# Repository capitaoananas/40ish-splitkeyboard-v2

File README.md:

# 40%ish Split Keyboard V2

A minimalist, 36-key split keyboard with 18 keys per half.

This is the **second generation** of the 40%ish split keyboard — an open-source, wireless-capable, DIY mechanical keyboard built for compact typing and clean design.

---

## What's New in V2

- **Easier reversing** – solder bridges allow mirrored PCB assembly without flipping the MCU
- **Wireless support** – built for the Nice!Nano V2 with RMK firmware and VIA configurability
- **Sandwich case support** – mounting holes added for plate/PCB/plate builds

---

## Features

- **Split layout** – 18 keys per side (36 total), column-staggered
- **MX hotswap** – change your switches anytime, no soldering needed
- **Wireless** – powered by Nice!Nano V2 + ZMK or RMK
- **Fully open-source** – PCB, firmware, case files

---

## Bill of Materials (BOM)
| Part                                 | Quantity | Price  | Link                                                                                                                                                                                                                                                                                                                                                                                                                                                                                          | Notes                                                      |
| ------------------------------------ | -------- | ------ | --------------------------------------------------------------------------------------------------------------------------------------------------------------------------------------------------------------------------------------------------------------------------------------------------------------------------------------------------------------------------------------------------------------------------------------------------------------------------------------------- | ---------------------------------------------------------- |
| PCB                                  | 5        | $19.31 | [JLCPCB](https://jlcpcb.com/)                                                                                                                                                                                                                                                                                                                                                                                                                                                                 | 5 is the minimum order quantity                            |
| Nice!Nano V2 clone                         | 2        | $ 7.8 | [aliexpress](https://pt.aliexpress.com/item/1005001621678794.html?spm=a2g0o.productlist.main.1.5b16u0QYu0QYA4&algo_pvid=eb4ff18e-0b67-44a7-8160-7abccc82fb3a&algo_exp_id=eb4ff18e-0b67-44a7-8160-7abccc82fb3a-0&pdp_ext_f=%7B%22order%22%3A%221021%22%2C%22eval%22%3A%221%22%7D&pdp_npi=4%40dis%21EUR%213.31%213.31%21%21%2127.23%2127.23%21%40211b80f717518012405113990e12af%2112000016846541261%21sea%21PT%216372042523%21X&curPageLogUid=jzaKSfne2bd1&utparam-url=scene%3Asearch%7Cquery_from%3A#nav-description)                                                                                                                                                                                                                                                                                                                                                                                                                                       | not the most ideal but really cheap                        |
| Mill Max Socket Pins                 | 48       | $9.18  | [Kris Cables](https://kriscables.com/product/mill-max-socket-pins/)                                                                                                                                                                                                                                                                                                                                                                                                                           |  |
| Microcontroller Hotswap Sockets      | 4        | $8.07  | [aliexpress](https://www.aliexpress.us/item/4001122376295.html?spm=a2g0o.productlist.main.1.5b1b2f7dvb20qw&algo_pvid=7361f9d9-8dab-4ced-844c-6e23df0449e3&algo_exp_id=7361f9d9-8dab-4ced-844c-6e23df0449e3-0&pdp_ext_f=%7B%22order%22%3A%222335%22%2C%22eval%22%3A%221%22%7D&pdp_npi=4%40dis%21EUR%212.52%212.52%21%21%212.89%212.89%21%40211b680e17517351193655082ed694%2110000014593481347%21sea%21PT%216372042523%21X&curPageLogUid=48AqA6mUIZQj&utparam-url=scene%3Asearch%7Cquery_from%3A)                                                                                                                                                                                                                                                                                                                                                                                                                   |                          |
| Haimu x Geon Silent Tactile Switches | 40       | $49.38 | [Delta Key](https://deltakeyco.com/collections/geon-switches/products/haimu-x-geon-hg-yellow-silent-tactile-switches)                                                                                                                                                                                                                                                                                                                                                                         | Sold in packs of 10, 36 needed                         |
| SDA keycaps                          | 1 set    | $23.50 | [amazon](https://www.amazon.com/YMDK-Profile-Keyset-Mechanical-Keyboard/dp/B07S18VCDN?ref_=ast_sto_dp&th=1)                                                                                                                                                                                                                                                                                                                                                                                   | Cheap and good                                             |
| Kailh hotswap sockets                | 36       | $6.67  | [aliexpress](https://pt.aliexpress.com/item/32951252318.html?spm=a2g0o.productlist.main.21.5090vkJPvkJPra&algo_pvid=acb05e60-2951-413b-91f9-12cc7be20dbc&algo_exp_id=acb05e60-2951-413b-91f9-12cc7be20dbc-20&pdp_ext_f=%7B%22order%22%3A%2279%22%2C%22eval%22%3A%221%22%7D&pdp_npi=4%40dis%21EUR%215.68%215.68%21%21%216.49%216.49%21%402103867617511082823454226eeda5%2112000036652544705%21sea%21PT%216372042523%21X&curPageLogUid=dALRGMcuMEGW&utparam-url=scene%3Asearch%7Cquery_from%3A) | aliexpress is awesome                                      |
|                                      |          |        | 

**Total: $123.91**

<dub>Prices include shipping<dub>

---

## Keyboard overview

### PCB

The PCB was made in Kicad

Schematic             |  PCB
:-------------------------:|:-------------------------:
  |  

### Case

The case was made in Fusion in a sandwich style case

Plate             |  Bottom
:-------------------------:|:-------------------------:
  |  

### Final Renders

Side             |  Top
:-------------------------:|:-------------------------:
  |  

---

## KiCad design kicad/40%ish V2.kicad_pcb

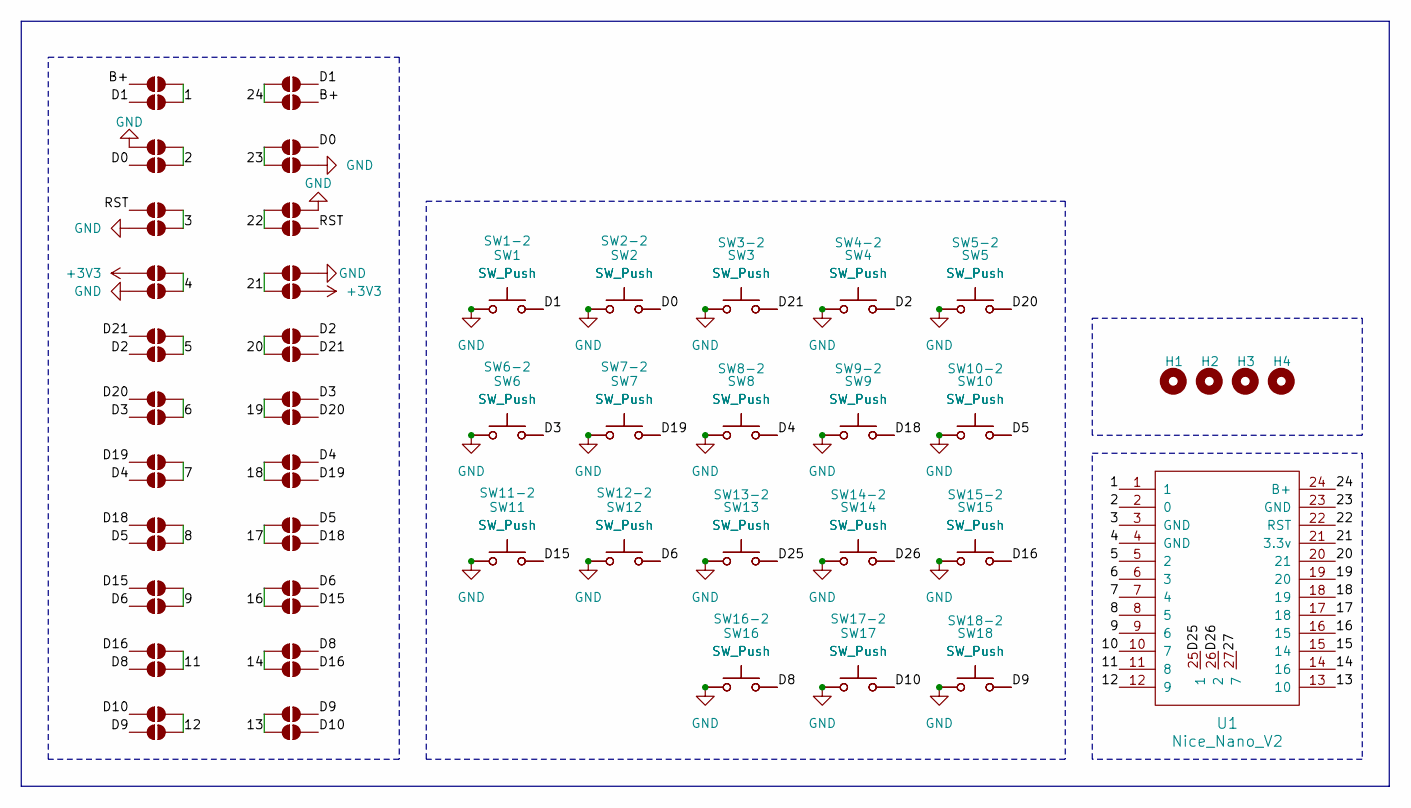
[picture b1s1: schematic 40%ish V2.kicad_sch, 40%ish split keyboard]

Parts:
H1, H2, H3, H4: MountingHole; MountingHole_3.2mm_M3
JP1, JP2, JP3, JP4, JP5, JP6, JP7, JP8, JP9, JP10, JP11, JP12, JP13, JP14, JP15, JP16, JP17, JP18, JP19, JP20, JP21, JP22, JP23, JP24, JP25, JP26, JP27, JP28, JP29, JP30, JP33, JP34, JP35, JP36, JP37, JP38, JP39, JP40, JP41, JP42, JP45, JP46, JP47, JP48: SolderJumper_2_Open; SolderJumper-2_P1.3mm_Open_TrianglePad1.0x1.5mm
SW1, SW1-2, SW2, SW2-2, SW3, SW3-2, SW4, SW4-2, SW5, SW5-2, SW6, SW6-2, SW7, SW7-2, SW8, SW8-2, SW9, SW9-2, SW10, SW10-2, SW11, SW11-2, SW12, SW12-2, SW13, SW13-2, SW14, SW14-2, SW15, SW15-2, SW16, SW16-2, SW17, SW17-2: SW_Push; MX-Hotswap-1U
SW18, SW18-2: SW_Push; MX-Hotswap-1.5U
U1: Nice_Nano_V2

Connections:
+3V3: JP25.1 (A), JP28.1 (A)
/1: JP13.2 (B), JP14.2 (B), U1.1
/2: JP17.2 (B), JP18.2 (B), U1.2 (0)
/3: JP21.2 (B), JP22.2 (B), U1.3 (GND)
/4: JP25.2 (B), JP26.2 (B), U1.4 (GND)
/5: JP1.2 (B), JP2.2 (B), U1.5 (2)
/6: JP3.2 (B), JP4.2 (B), U1.6 (3)
/7: JP9.2 (B), JP10.2 (B), U1.7 (4)
/8: JP11.2 (B), JP12.2 (B), U1.8 (5)
/9: JP29.2 (B), JP30.2 (B), U1.9 (6)
/10: U1.10 (7)
/11: JP33.2 (B), JP34.2 (B), U1.11 (8)
/12: JP35.2 (B), JP36.2 (B), U1.12 (9)
/13: JP47.2 (B), JP48.2 (B), U1.13 (10)
/14: JP45.2 (B), JP46.2 (B), U1.14 (16)
/15: U1.15 (14)
/16: JP41.2 (B), JP42.2 (B), U1.16 (15)
/17: JP39.2 (B), JP40.2 (B), U1.17 (18)
/18: JP37.2 (B), JP38.2 (B), U1.18 (19)
/19: JP7.2 (B), JP8.2 (B), U1.19 (20)
/20: JP5.2 (B), JP6.2 (B), U1.20 (21)
/21: JP27.2 (B), JP28.2 (B), U1.21 (3.3v)
/22: JP23.2 (B), JP24.2 (B), U1.22 (RST)
/23: JP19.2 (B), JP20.2 (B), U1.23 (GND)
/24: JP15.2 (B), JP16.2 (B), U1.24 (B+)
/27: U1.27 (7)
/B+: JP13.1 (A), JP16.1 (A)
/D0: JP18.1 (A), JP19.1 (A), SW2.2, SW2-2.2
/D1: JP14.1 (A), JP15.1 (A), SW1.2, SW1-2.2
/D2: JP2.1 (A), JP5.1 (A), SW4.2, SW4-2.2
/D3: JP4.1 (A), JP7.1 (A), SW6.2, SW6-2.2
/D4: JP10.1 (A), JP37.1 (A), SW8.2, SW8-2.2
/D5: JP12.1 (A), JP39.1 (A), SW10.2, SW10-2.2
/D6: JP30.1 (A), JP41.1 (A), SW12.2, SW12-2.2
/D8: JP34.1 (A), JP45.1 (A), SW16.2, SW16-2.2
/D9: JP36.1 (A), JP47.1 (A), SW18.2, SW18-2.2
/D10: JP35.1 (A), JP48.1 (A), SW17.2, SW17-2.2
/D15: JP29.1 (A), JP42.1 (A), SW11.2, SW11-2.2
/D16: JP33.1 (A), JP46.1 (A), SW15.2, SW15-2.2
/D18: JP11.1 (A), JP40.1 (A), SW9.2, SW9-2.2
/D19: JP9.1 (A), JP38.1 (A), SW7.2, SW7-2.2
/D20: JP3.1 (A), JP8.1 (A), SW5.2, SW5-2.2
/D21: JP1.1 (A), JP6.1 (A), SW3.2, SW3-2.2
/D25: SW13.2, SW13-2.2, U1.25 (1)
/D26: SW14.2, SW14-2.2, U1.26 (2)
/RST: JP21.1 (A), JP24.1 (A)
GND: JP17.1 (A), JP20.1 (A), JP22.1 (A), JP23.1 (A), JP26.1 (A), JP27.1 (A), SW1.1, SW1-2.1, SW2.1, SW2-2.1, SW3.1, SW3-2.1, SW4.1, SW4-2.1, SW5.1, SW5-2.1, SW6.1, SW6-2.1, SW7.1, SW7-2.1, SW8.1, SW8-2.1, SW9.1, SW9-2.1, SW10.1, SW10-2.1, SW11.1, SW11-2.1, SW12.1, SW12-2.1, SW13.1, SW13-2.1, SW14.1, SW14-2.1, SW15.1, SW15-2.1, SW16.1, SW16-2.1, SW17.1, SW17-2.1, SW18.1, SW18-2.1

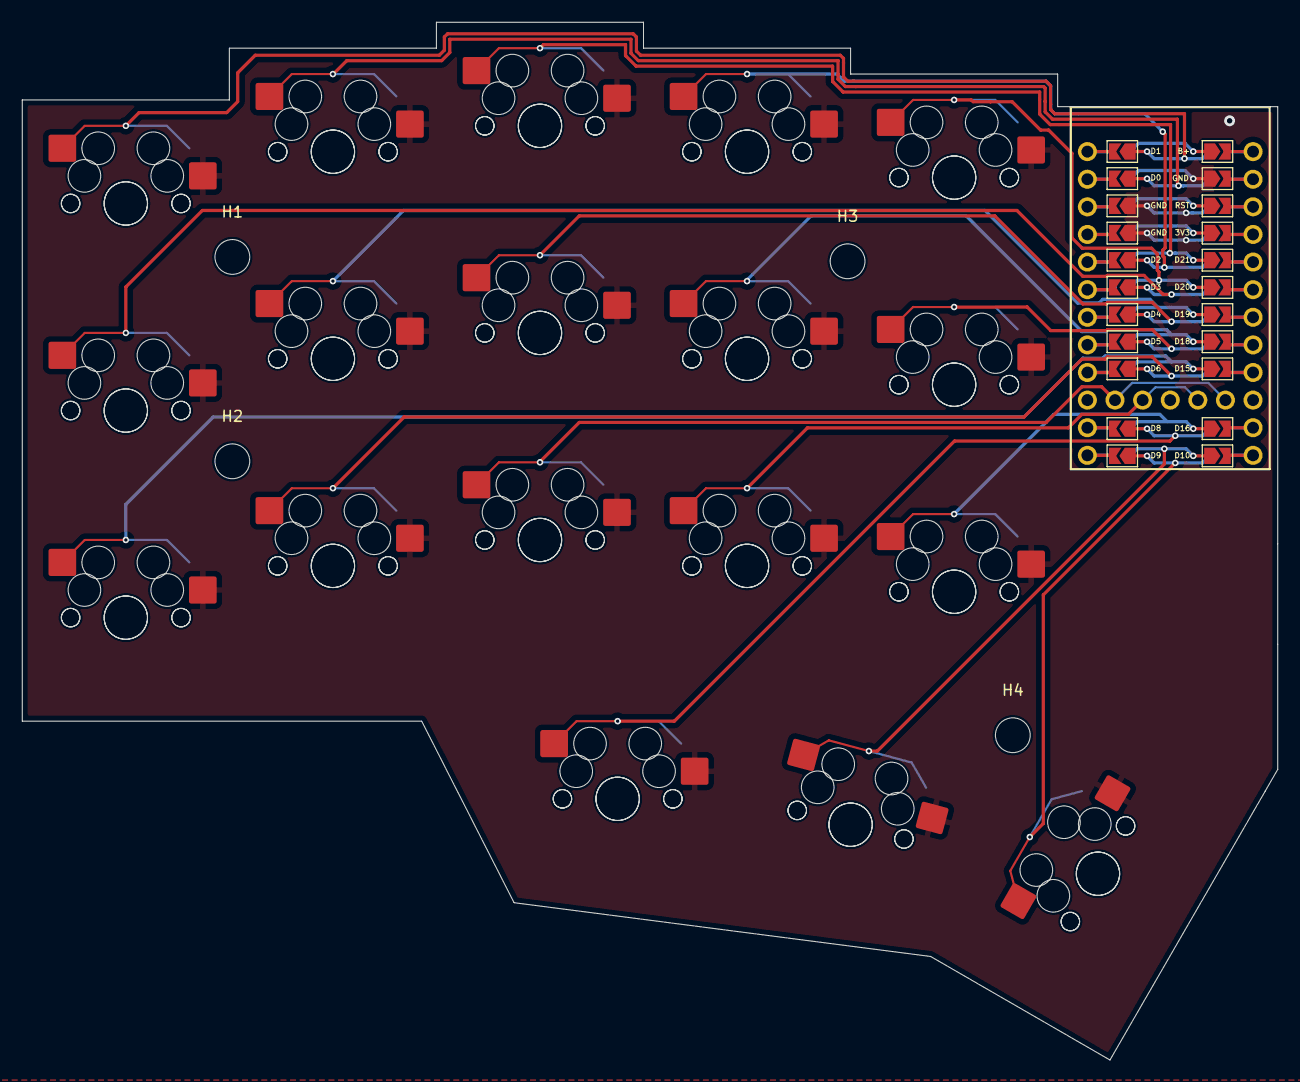
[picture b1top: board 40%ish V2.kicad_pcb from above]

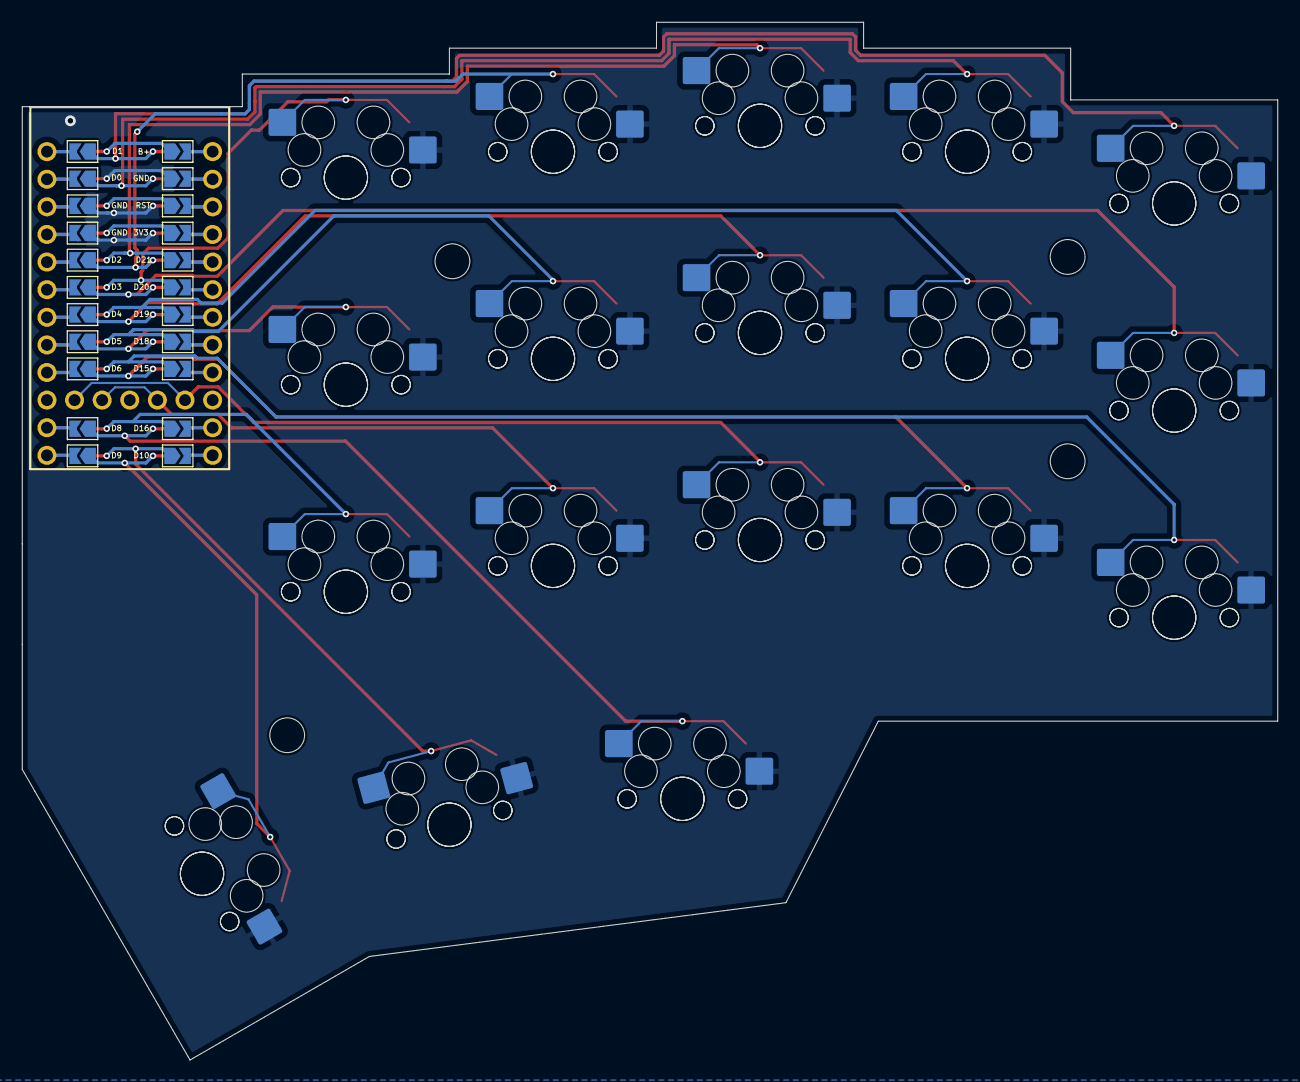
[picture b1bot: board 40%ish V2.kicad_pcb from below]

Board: 2 copper layers, 115.5 x 95.5 mm, 85 parts (40 on the bottom side), 44 nets.

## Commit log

2025-05-30 add journal and kicad files
2025-05-30 actually add journal and rename folder
2025-06-01 add new schematic
2025-06-01 update journal
2025-06-01 fix: may 32nd
2025-06-02 add new files and journal
2025-06-03 update PCB
2025-06-03 update time spent
2025-06-30 PCB done
2025-07-05 make 3D dir
2025-07-06 add 3d
2025-07-06 journal
2025-07-06 update bom
2025-07-06 update microcontroller
2025-07-06 update desk
2025-07-06 add total bom
2025-07-06 update format
2025-07-06 update format againg
